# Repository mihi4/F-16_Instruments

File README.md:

# Instruments used in my F-16 Simulator

This repository has been created to hold all the files I used to create the instrument's hardware for my [F-16 simulator](https://f16simulator.net)  
The Arduino part is in seperate repositories, since one Arduino controls more instruments. Those repos are linked in the README of each instrument.

Other instruments, once finished, will be added to this list.

[ALTIMETER](https://github.com/mihi4/F-16Altimeter)
(own repo because added before)

***

[eHSI](eHSI)

***

[RWR](rwr)

***

[VVI/AOA](vvi_aoa)

***
  
[HYDPRESS](hydpress)

***

[FQI](fuelgauge)

***

[EPU FUEL](epuFuel)

***

[CautionPanel](cautionPanel)

***

## !!! Use those files at your own risk !!!

All the files are free to use under the GNUGPLv3

If you find those files useful and would like to support me with an icecream, coffee or pizza, you can use paypal.me to do so ;)  
[Paypal.me](https://paypal.me/MichiHirczy)

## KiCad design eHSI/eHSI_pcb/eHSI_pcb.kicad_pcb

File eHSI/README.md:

### eHSI

All the parts are designed with FreeCAD, you can modify the files as you like.  

I'm using the following additional parts to build the eHSI:  

Display: [3.5" 640x480 LCD from Ali](https://www.aliexpress.com/item/1005007806914783.html) (Search for "3.5 inch LCD", if the link expired)  
Encoders: [SMD EC11 Encoder](https://www.aliexpress.com/item/1005004240213420.html) with 15mm shaft (Search for "EC11 SMD rotary encoder", if the link expired)  
Button: It's a 6.7x4.1mm SMD tactile button (Link on Ali already expired)  
GX12-6 Connector

The display is powered by a 5V MiniUSB and connects to the PC via MiniHDMI.  
  
I connect the encoders and the button to an ArduinoPro which will have my IOController firmware on it.  
You can use any input board that supports encoders as you like.

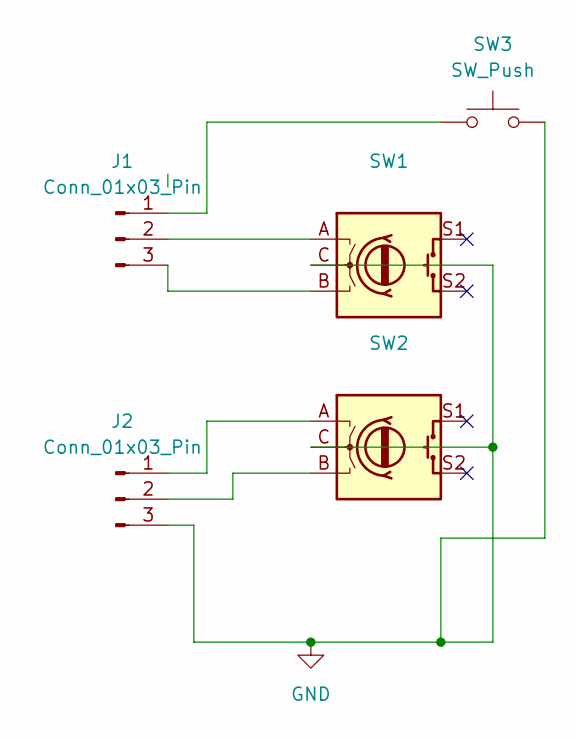
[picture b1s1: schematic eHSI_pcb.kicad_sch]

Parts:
J1, J2: Conn_01x03_Pin; PinHeader_1x03_P2.54mm_Vertical
SW1, SW2: RotaryEncoder_Switch; RotaryEncoder_Alps_EC11E-Switch_Vertical_H20mm_SMD
SW3: SW_Push; SW_DIP_SPSTx01_Slide_6.7x4.1mm_W6.73mm_P2.54mm_LowProfile_J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

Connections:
GND: J2.3, SW1.C, SW2.C, SW3.2
unnamed: J1.1, SW3.1
unnamed: J1.2, SW1.A
unnamed: J1.3, SW1.B
unnamed: J2.1, SW2.A
unnamed: J2.2, SW2.B

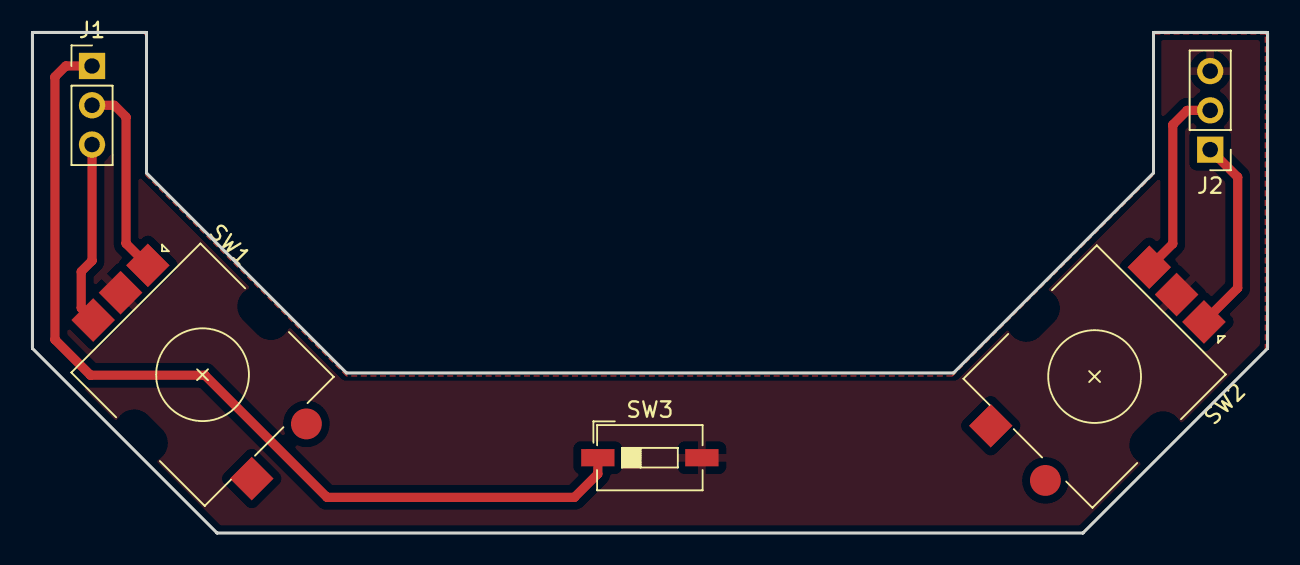
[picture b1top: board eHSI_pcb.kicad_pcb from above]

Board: 2 copper layers, 79.9 x 32.4 mm, 5 parts (0 on the bottom side), 6 nets.

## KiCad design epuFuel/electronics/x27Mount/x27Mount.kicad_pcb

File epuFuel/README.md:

# EPU FUEL Gauge

The EPU FUEL Gauge is driven by the [BMSAIT-RightAuxConsole](https://github.com/mihi4/F-16_BMSAITRightAUX)

Parts used:
- 1 X27.168 stepper motor

Info on my website:  
[EPUFUEL](https://f16simulator.net/wp/en/2023/10/01/new-rightaux-instruments/)

## !!! Use those files at your own risk !!!

All the files are free to use under the GNUGPLv3

If you would like to support me with an icecream, coffee or pizza, you can use paypal.me to to so ;)  
[Paypal.me](https://paypal.me/MichiHirczy)

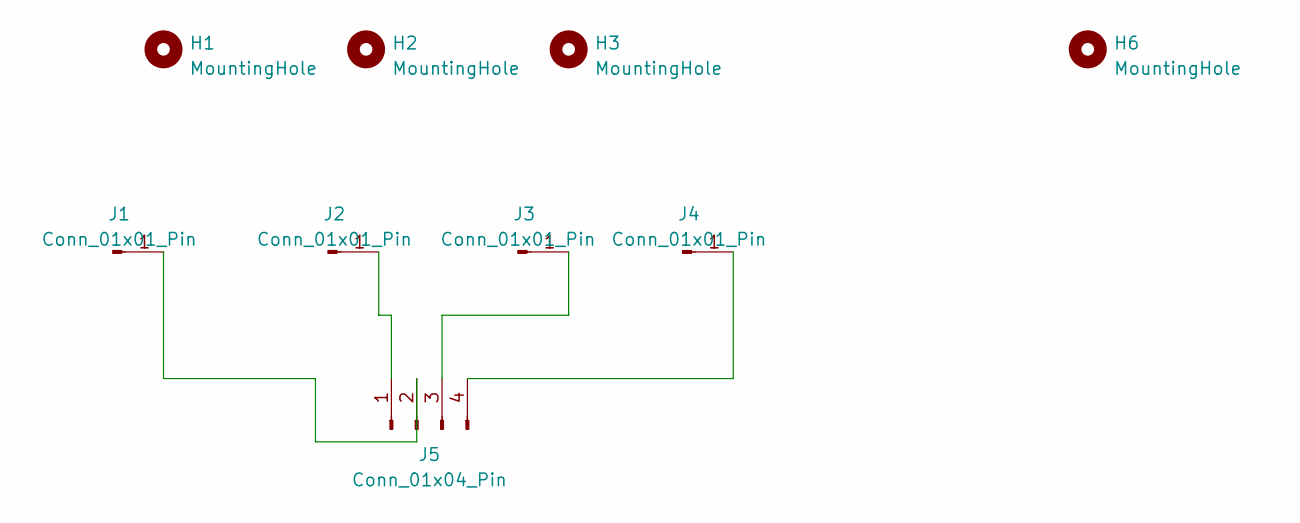
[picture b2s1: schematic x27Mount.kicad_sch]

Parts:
H1: MountingHole; MountingHole_2.7mm
H2, H3: MountingHole; MountingHole_3.2mm_M3
H6: MountingHole; MountingHole_4.5mm
J1, J2, J3, J4: Conn_01x01_Pin; PinHeader_1x01_P2.54mm_Vertical
J5: Conn_01x04_Pin; PinHeader_1x04_P2.54mm_Horizontal

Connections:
unnamed: J1.1, J5.2
unnamed: J2.1, J5.1
unnamed: J3.1, J5.3
unnamed: J4.1, J5.4

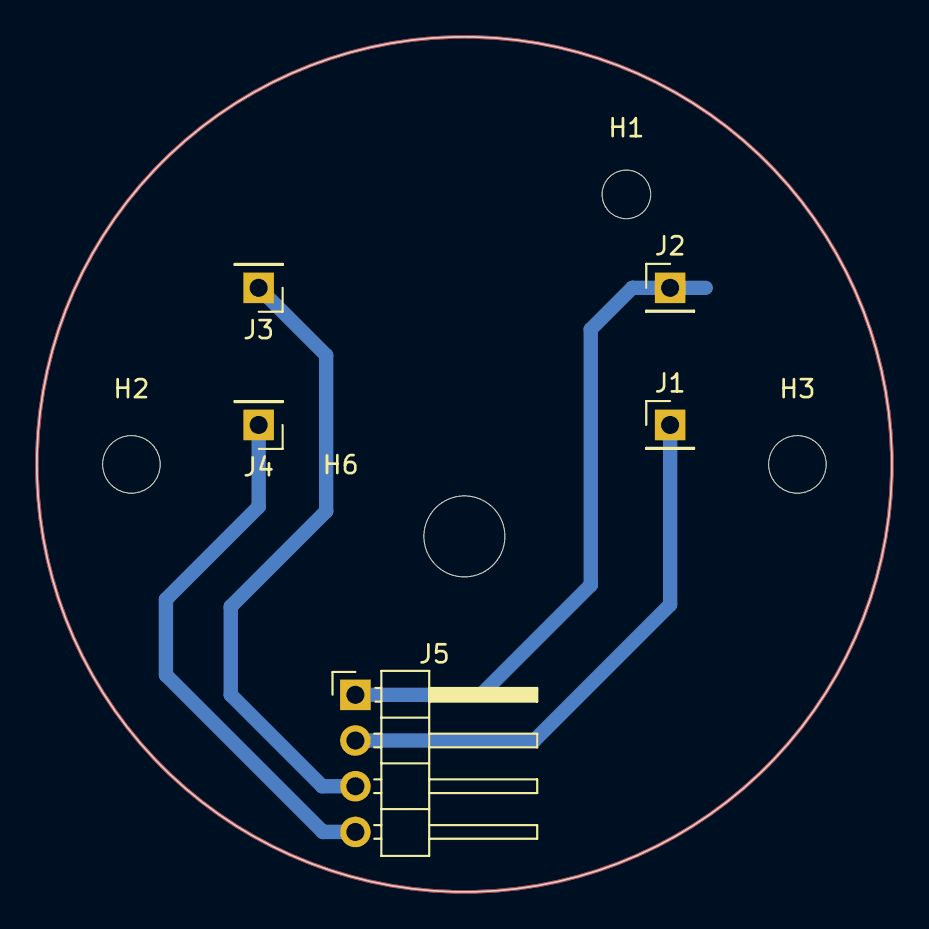
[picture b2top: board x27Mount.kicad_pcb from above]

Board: 2 copper layers, 47.5 x 47.5 mm, 9 parts (0 on the bottom side), 4 nets.

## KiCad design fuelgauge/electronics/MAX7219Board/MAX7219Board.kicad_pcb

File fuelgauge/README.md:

# FUEL QTY Gauge

The whole FUEL QTY Gauge is driven by the ~~[BMSAIT-RightAuxConsole](https://github.com/mihi4/F-16_BMSAITRightAUX)~~ [IOController](https://github.com/mihi4/F-16_IOController)

Parts used:
- 2 SG90/9g miniservos
- 1 CL2351AW 5-digit-7segment-display (CommonCathode, 0.23" white)

Info on my website:  
[FQI](https://f16simulator.net/wp/en/2023/07/07/fuelquantityindicator-in-the-works/)

## !!! Use those files at your own risk !!!

All the files are free to use under the GNUGPLv3

If you would like to support me with an icecream, coffee or pizza, you can use paypal.me to to so ;)  
[Paypal.me](https://paypal.me/MichiHirczy)

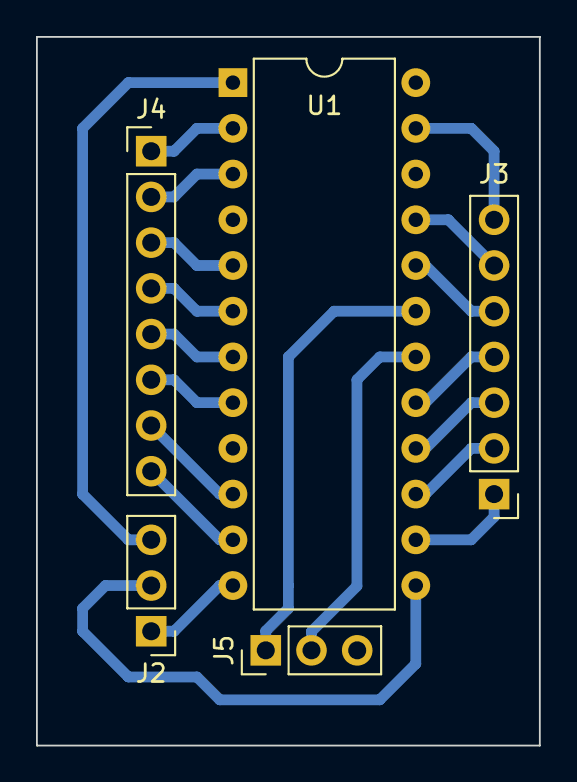
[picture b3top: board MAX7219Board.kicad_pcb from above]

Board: 2 copper layers, 27.9 x 39.4 mm, 5 parts (0 on the bottom side), 21 nets.

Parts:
J2: Data; PinHeader_1x03_P2.54mm_Vertical
J3: Segs; PinHeader_1x07_P2.54mm_Vertical
J4: Digits; PinHeader_1x08_P2.54mm_Vertical
J5: PWR; PinHeader_1x03_P2.54mm_Vertical
U1: MAX7219; DIP-24_W10.16mm

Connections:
+5V: J5.1, U1.19 (V+)
GND: J5.3, U1.4 (GND), U1.9 (GND)
unnamed: J2.1, U1.12 (LOAD)
unnamed: J2.2, U1.13 (CLK)
unnamed: J2.3, U1.1 (DIN)
unnamed: J3.1, U1.14 (SEG_A)
unnamed: J3.2, U1.15 (SEG_F)
unnamed: J3.3, U1.16 (SEG_B)
unnamed: J3.4, U1.17 (SEG_G)
unnamed: J3.5, U1.20 (SEG_C)
unnamed: J3.6, U1.21 (SEG_E)
unnamed: J3.7, U1.23 (SEG_D)
unnamed: J4.1, U1.2 (DIG_0)
unnamed: J4.2, U1.3 (DIG_4)
unnamed: J4.3, U1.5 (DIG_6)
unnamed: J4.4, U1.6 (DIG_2)
unnamed: J4.5, U1.7 (DIG_3)
unnamed: J4.6, U1.8 (DIG_7)
unnamed: J4.7, U1.10 (DIG_5)
unnamed: J4.8, U1.11 (DIG_1)
unnamed: J5.2, U1.18 (ISET)

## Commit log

2023-07-08 Update hydpress.FCStd, hydpress.FCStd1, and 4 more files...
2023-07-08 Update README.md, altimeter-GearBigMod0_5.3mf, and 52 more files...
2023-07-08 Update altimeter-GearBigMod0_5.3mf, altimeter-GearBigStepper.3mf, and 24 more files...
2023-07-08 Update VVI_AOA-CommonFront.3mf, VVI_AOA-CommonGlassSpacer.3mf, and 19 more files...
2023-07-08 Update README.md, altimeterParts.FCStd, and 4 more files...
2023-10-02 Update epuFuel.FCStd, epuFuel.FCStd1, and 11 more files...
2023-10-04 Update cautionPanel.FCStd, cautionPanel.FCStd1, and 15 more files...
2024-03-23 added draft info
2026-05-09 eHSI added
2026-05-15 Update rwr.png, CAD.png, and 9 more files...
2026-05-15 Create README.md for RWR project
    Add initial README with project details and components used.
